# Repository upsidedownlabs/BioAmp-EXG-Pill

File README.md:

BioAmp EXG Pill is a small (2.54 X 1.00 cm) and elegant Analog Front End (AFE) board for BioPotential signal acquisition that you can use with any 5v Micro Controller Unit (MCU) with an ADC. It is capable of recording publication grade BioPotential signals like ECG, EMG, EOG, and EEG without the inclusion of any dedicated Hardware/Software filter, see [BioAmp EXG Pill v0.7 intro video](https://www.youtube.com/watch?v=-G3z9fvQnuw) for more info. The v1.0 of BioAmp EXG pill provides even more flexibilty with configuration option for Gain, BandPass, Filter, and Electrodes.

| Connection      |  Configuration |
| :-------------------------: | :-------------------------: |
|   | |

| Basic Arduino Circuit           |  Electromyography (EMG) |
| :-------------------------: | :-------------------------: |
|   | |

| Electrooculography (EOG) Horizontal           |  Electrooculography (EOG) Vertical |
| :-------------------------: | :-------------------------: |
|   | |

| Electrocardiography (ECG) Lead 1           |  Electroencephalography (EEG) |
| :-------------------------: | :-------------------------: |
|   | |

## Software
BioAmp EXG Pill works with any 5V microcontroller with an ADC like Arduino UNO/Nano or you can use dedicated 5v compatible ADC like ADS1115. To help with signal processing and cleaning you can use the included Arduino example sketches listed below.

| No. | Program| Description |
| ---- | ---- | ---- |
|1 | [FixedSampling](software/FixedSampling)| Sample from ADC at a fixed rate for easy processing of signal.|
|2 | [EMGFilter](software/EMGFilter)| A 74.5 - 149.5 Hz band pass filter sketch for clean Electromyography.|
|3 | [ECGFilter](software/ECGFilter)| A 0.5 - 44.5 Hz band-pass filter sketch for clean Electrocardiography.|
|4 | [EOGFilter](software/EOGFilter)| A 0.5 - 19.5 Hz band-pass filter sketch for clean Electrooculography.|
|5 | [EEGFilter](software/EEGFilter)| A 0.5 - 29.5 Hz band-pass filter sketch for clean Electroencephalography.|
|6 | [EMGEnvelop](software/EMGEnvelop)| EMG signal envelop detection for robotics and biomedical applications.|
|7 | [LEDBarGraph](software/LEDBarGraph)| LED bar graph showing EMG amplitude.|
|8 | [ServoControl](software/ServoControl)| Servo motor control with EMG.|
|9 | [HeartBeatDetection](software/HeartBeatDetection)| Standard deviation based heart beat detection algorithm.|
|10 | [EyeBlinkDetection](software/EyeBlinkDetection)|EOG based eye blink detection.|
|11 | [DrowsinessDetection](software/DrowsinessDetection)| Drowsiness detection using eye blink detection.|
|12 | [ClawController](software/ClawController)| Servo claw controller |
|13 | [EOGPhotoCaptureBLE](software/EOGPhotoCaptureBLE)| EOG based photo clicking machine using ESP32 BLE |
|14 | [Faster_HeartRateDetection](software/Faster_HeartRateDetection)| Faster and more optimzed calculation of BPM |
|15 | [OLED_BPM](software/OLED_BPM)| Display BPM values on OLED Screen|

To-Do:

| No. | Program| Description |
| ---- | ---- | ---- |
|1 | HeartRate | Heart rate calculation with ECG.|
|2 | BrainWaves | Brain waves amplitude with FFT.|
|3 | EOGController | EOG based eye movement detection (left/right) to create a game controller.|

## Hardware

BioAmp EXG Pill has been created using KiCad and all the design files can be found under [hardware](hardware/) folder, including production [Gerber](hardware/gerbers) files. Images below shows a quick overview of the hardware design.

| PCB Front           |  PCB Back |
| :-------------------------: | :-------------------------: |
|   |  |

| Dimensions            |  Schematic  |
| :-------------------------: | :-------------------------: |
|   |  |

## License

| Licenses Facts              |  OSHWA Certification |
| :-------------------------: | :-------------------------: |
|   |  |

#### Hardware
CERN Open Hardware License Version 2 - Strongly Reciprocal ([CERN-OHL-S-2.0](https://spdx.org/licenses/CERN-OHL-S-2.0.html)).

#### Software
MIT open source [license](http://opensource.org/licenses/MIT).

#### Documentation:
<br />This work is licensed under a <a rel="license" href="http://creativecommons.org/licenses/by/4.0/">Creative Commons Attribution 4.0 International License</a>.

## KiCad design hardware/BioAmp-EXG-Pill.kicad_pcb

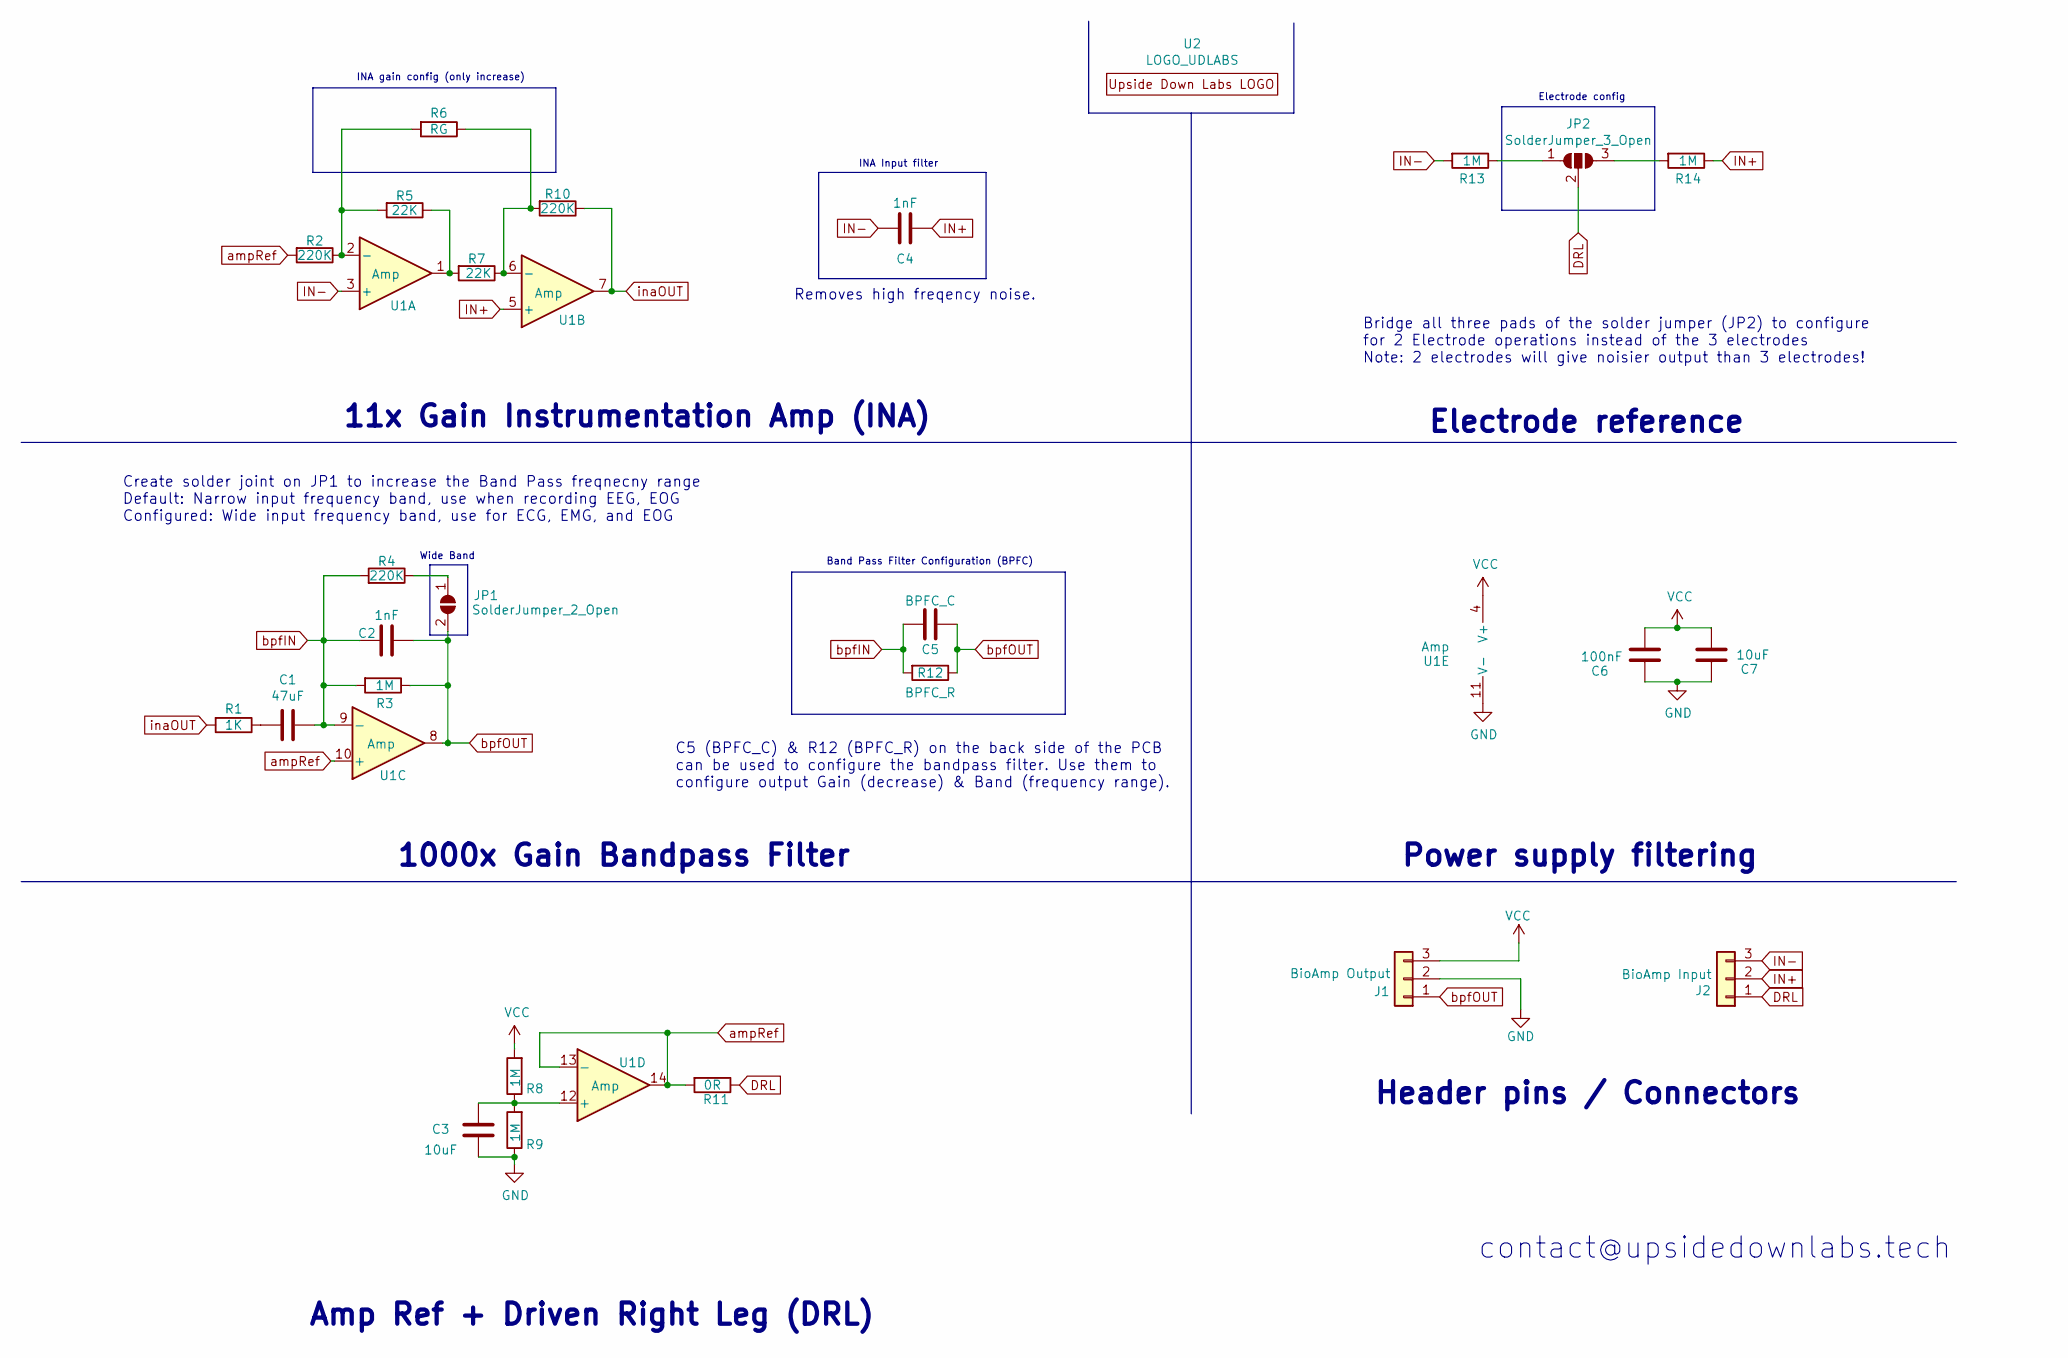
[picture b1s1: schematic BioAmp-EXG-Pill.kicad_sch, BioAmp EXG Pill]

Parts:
C1: 47uF; C_0805_2012Metric_Pad1.18x1.45mm_HandSolder
C2, C4: 1nF; C_0603_1608Metric_Pad1.08x0.95mm_HandSolder
C3, C7: 10uF; C_0603_1608Metric_Pad1.08x0.95mm_HandSolder
C5: BPFC_C; C_0603_1608Metric_Pad1.08x0.95mm_HandSolder
C6: 100nF; C_0603_1608Metric_Pad1.08x0.95mm_HandSolder
J1: BioAmp Output; PinHeader_1x03_P2.54mm_Vertical
J2: BioAmp Input; PinHeader_1x03_P2.54mm_Vertical
JP1: SolderJumper_2_Open; SolderJumper-2_P1.3mm_Open_RoundedPad1.0x1.5mm
JP2: SolderJumper_3_Open; SolderJumper-3_P1.3mm_Open_RoundedPad1.0x1.5mm
R1: 1K; R_0603_1608Metric_Pad0.98x0.95mm_HandSolder
R2, R4, R10: 220K; R_0603_1608Metric_Pad0.98x0.95mm_HandSolder
R3, R8, R9, R13, R14: 1M; R_0603_1608Metric_Pad0.98x0.95mm_HandSolder
R5, R7: 22K; R_0603_1608Metric_Pad0.98x0.95mm_HandSolder
R6: RG; R_0603_1608Metric_Pad0.98x0.95mm_HandSolder
R11: 0R; R_0603_1608Metric_Pad0.98x0.95mm_HandSolder
R12: BPFC_R; R_0603_1608Metric_Pad0.98x0.95mm_HandSolder
U1: Amp; TSSOP-14_4.4x5mm_P0.65mm
U2: LOGO_UDLABS; EXG

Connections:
DRL: J2.1, JP2.2 (C), R11.1; also elsewhere on the board
GND: C3.2, C6.1, C7.1, J1.2, R9.1, U1.11 (V-); also elsewhere on the board
IN+: C4.1, J2.2, R14.1, U1.5 (+); also elsewhere on the board
IN-: C4.2, J2.3, R13.2, U1.3 (+); also elsewhere on the board
unnamed: C1.2, R1.1
unnamed: C3.1, R8.1, R9.2, U1.12 (+)
unnamed: JP1.1 (A), R4.1
unnamed: JP2.1 (A), R13.1
unnamed: JP2.3 (B), R14.2
unnamed: R2.1, R5.2, R6.2, U1.2 (-)
unnamed: R5.1, R7.2, U1.1
unnamed: R6.1, R7.1, R10.2, U1.6 (-)
VCC: C6.2, C7.2, J1.3, R8.2, U1.4 (V+); also elsewhere on the board
ampRef: R2.2, R11.2, U1.10 (+), U1.13 (-), U1.14
bpfIN: C1.1, C2.2, C5.2, R3.2, R4.2, R12.2, U1.9 (-)
bpfOUT: C2.1, C5.1, J1.1, JP1.2 (B), R3.1, R12.1, U1.8; also elsewhere on the board
inaOUT: R1.2, R10.1, U1.7

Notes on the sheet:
contact@upsidedownlabs.tech
1000x Gain Bandpass Filter
Create solder joint on JP1 to increase the Band Pass freqnecny range Default: Narrow input frequency band, use when recording EEG, EOG Configured: Wide input frequency band, use for ECG, EMG, and EOG
Band Pass Filter Configuration (BPFC)
Electrode config
C5 (BPFC_C) & R12 (BPFC_R) on the back side of the PCB can be used to configure the bandpass filter. Use them to configure output Gain (decrease) & Band (frequency range).
Header pins / Connectors
11x Gain Instrumentation Amp (INA)
Bridge all three pads of the solder jumper (JP2) to configure for 2 Electrode operations instead of the 3 electrodes Note: 2 electrodes will give noisier output than 3 electrodes!
Power supply filtering
Amp Ref + Driven Right Leg (DRL)
Removes high freqency noise.
Wide Band
INA gain config (only increase)
Electrode reference
INA Input filter

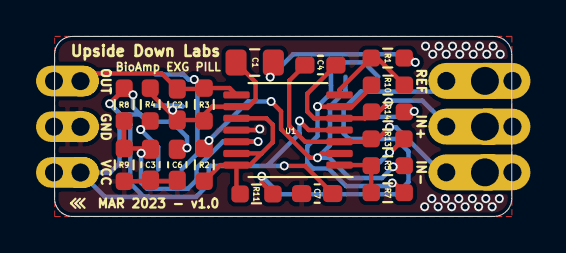
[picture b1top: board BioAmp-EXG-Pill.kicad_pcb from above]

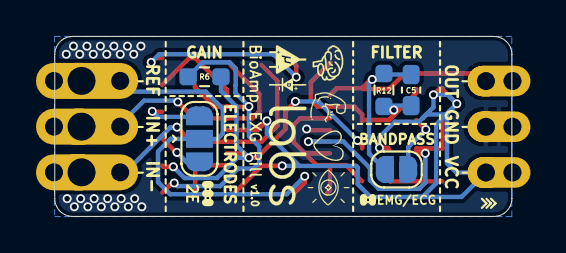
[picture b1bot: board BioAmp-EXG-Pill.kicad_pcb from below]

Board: 2 copper layers, 25.4 x 10.0 mm, 30 parts (6 on the bottom side), 17 nets.

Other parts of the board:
J1#2: BioAmp Output; PinHeader_1x03_P2.54mm_Vertical
J2#2, J2#3: BioAmp Input; PinHeader_1x03_P2.54mm_Vertical

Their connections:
DRL: J2#2.1, J2#3.1; also elsewhere on the board
GND: J1#2.2; also elsewhere on the board
IN+: J2#2.2, J2#3.2; also elsewhere on the board
IN-: J2#2.3, J2#3.3; also elsewhere on the board
VCC: J1#2.3; also elsewhere on the board
bpfOUT: J1#2.1; also elsewhere on the board

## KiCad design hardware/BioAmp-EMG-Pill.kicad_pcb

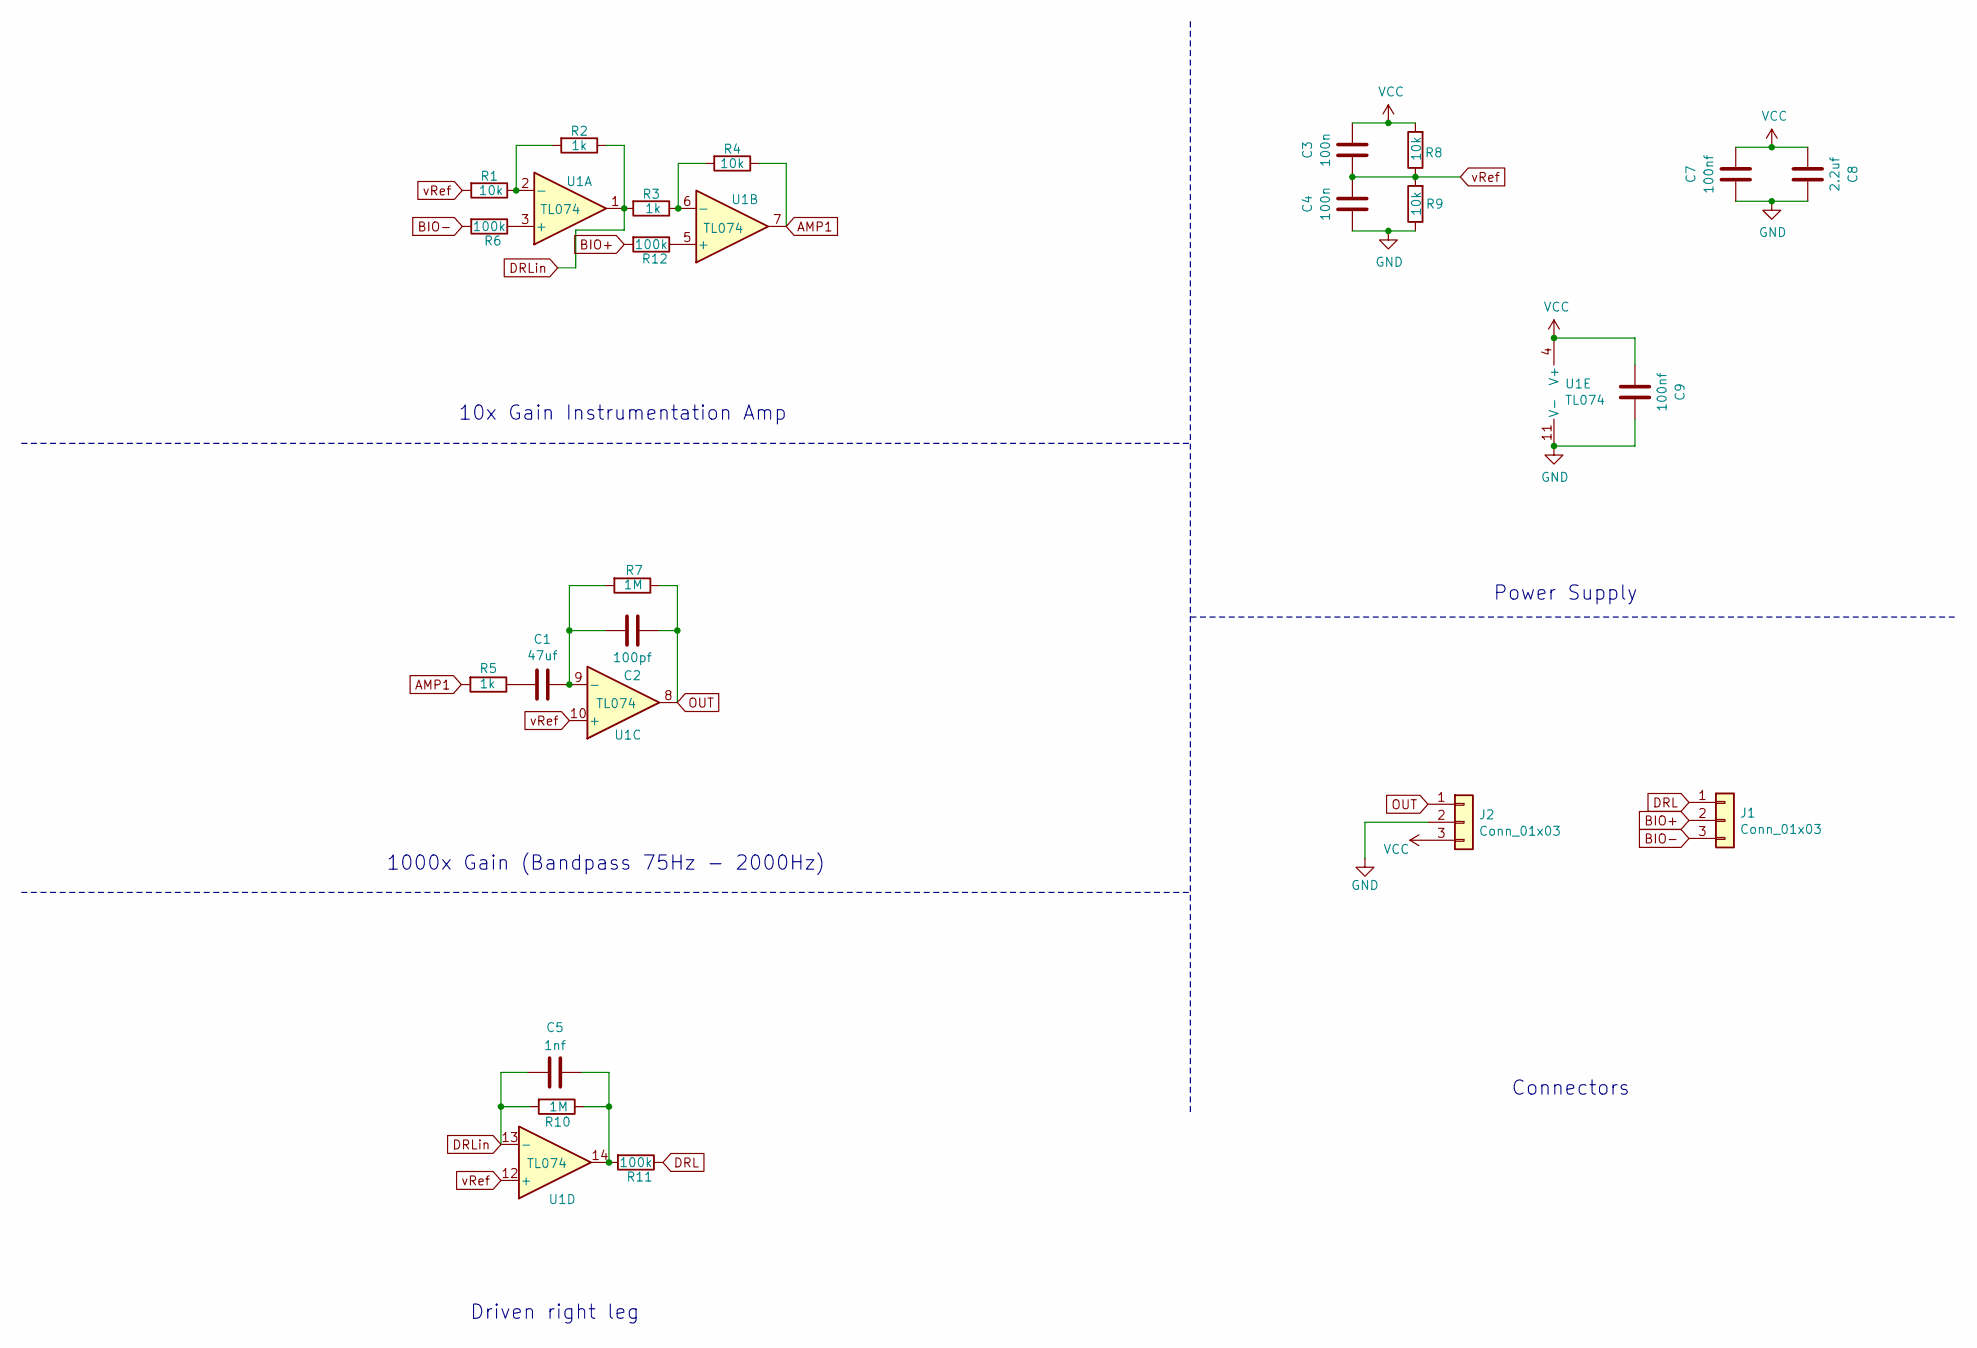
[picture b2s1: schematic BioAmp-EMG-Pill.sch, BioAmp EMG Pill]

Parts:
C1: 47uf; C_0805_2012Metric_Pad1.18x1.45mm_HandSolder
C2: 100pf; C_0603_1608Metric_Pad1.08x0.95mm_HandSolder
C3, C4: 100n; C_0603_1608Metric_Pad1.08x0.95mm_HandSolder
C5: 1nf; C_0603_1608Metric_Pad1.08x0.95mm_HandSolder
C7, C9: 100nf; C_0603_1608Metric_Pad1.08x0.95mm_HandSolder
C8: 2.2uf; C_0603_1608Metric_Pad1.08x0.95mm_HandSolder
J1, J2: Conn_01x03; PinHeader_1x03_P2.54mm_Vertical
R1, R4, R8, R9: 10k; R_0603_1608Metric_Pad0.98x0.95mm_HandSolder
R2, R3, R5: 1k; R_0603_1608Metric_Pad0.98x0.95mm_HandSolder
R6, R11, R12: 100k; R_0603_1608Metric_Pad0.98x0.95mm_HandSolder
R7, R10: 1M; R_0603_1608Metric_Pad0.98x0.95mm_HandSolder
U1: TL074; TSSOP-14_4.4x5mm_P0.65mm

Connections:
AMP1: R4.1, R5.2, U1.7
BIO+: J1.2, R12.2
BIO-: J1.3, R6.2
DRL: J1.1, R11.1
DRLin: C5.1, R2.1, R3.2, R10.2, U1.1, U1.13 (-)
GND: C4.2, C7.2, C8.1, C9.1, J2.2, R9.1, U1.11 (V-)
unnamed: C1.1, C2.2, R7.2, U1.9 (-)
unnamed: C1.2, R5.1
unnamed: C5.2, R10.1, R11.2, U1.14
unnamed: R1.1, R2.2, U1.2 (-)
unnamed: R3.1, R4.2, U1.6 (-)
unnamed: R6.1, U1.3 (+)
unnamed: R12.1, U1.5 (+)
OUT: C2.1, J2.1, R7.1, U1.8
VCC: C3.1, C7.1, C8.2, C9.2, J2.3, R8.2, U1.4 (V+)
vRef: C3.2, C4.1, R1.2, R8.1, R9.2, U1.10 (+), U1.12 (+)

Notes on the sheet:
10x Gain Instrumentation Amp
1000x Gain (Bandpass 75Hz - 2000Hz)
Driven right leg
Power Supply
Connectors

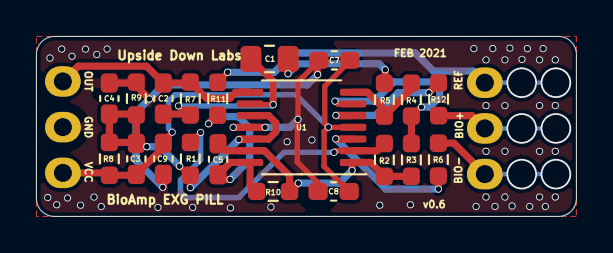
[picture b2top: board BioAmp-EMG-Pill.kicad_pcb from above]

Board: 2 copper layers, 30.0 x 10.0 mm, 23 parts (0 on the bottom side), 16 nets.

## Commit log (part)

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2021-01-27 add shematic
    Schematic for v0.1
2021-01-27 add back image of board
2021-01-27 add board dimensions image
2021-01-30 Update license
2021-01-30 rename image
2021-02-12 add 3D
2021-02-12 Upside Down Labs muscle image
2021-02-18 EMG Pill v0.6 back
2021-02-18 EMG Pill v0.6 Front
2021-02-18 EMG Pill v0.6 dimensions
2021-03-12 Silk layer images
2021-04-10 KiCAD files BioAmp EXG Pill v0.7
    KiCAD (5.1.9) files for Upside Down Labs BioAmp EXG Pill v0.7
2021-04-10 BioAmp EXG panel gerbers
    These are the gerber files for BioAmp EXG Panel, which provides 21 BioAmp EXG Pill on a single PCB.
2021-04-10 BioAmp EXG pill gerbers
    These are the gerber files for BioAmp EXG Pill v0.7
2021-04-10 KiCAD: BioAmp EXG Panel
    KiCAD files for BioAmp EXG Panel which provides 21 BioAmp EXG Pills on a signale PCB.
2021-04-10 Dimensions: BioAmp EXG Pill v0.7
    This image shows the dimensions and the properties (layers) of the BioAmp EXG Pill v0.7 (Taken from KiCAD).
2021-04-10 Schematic: BioAmp EXG Pill v0.7
    This image shows the schematic diagram of the BioAmp EXG Pill v0.7 (Taken from KiCAD).
2021-04-10 BioAmp EXG Pill v0.7
    These image shows the BioAmp EXG Pill v0.7 (Taken from KiCAD and edited with GIMP).
2021-04-10 Magic: BioAmp EXG Pill v0.7
    This image shows design flexibility and the elegance that Upside Down Labs BioAmp EXG Pill v0.7 comes with.
2021-04-10 Update licence
    minimal changes for better alignment and for less markup warnings.
2021-04-10 Update readme
    Updated links and text for BioAmp EXG Pill 0.7
2021-04-11 Update README.md
    Description updated
2021-04-15 Update README.md
    Add shield for Hackaday documentation page!
2021-04-18 OSHW mark image
2021-04-18 Update Readme
    Include OSH Park shared PCB link
2021-04-30 EEG Filter
    Arduino code for recording EEG using BioAmp EXG Pill.
2021-05-01 Update EEGFilter
    Minor code changes implemented.
2021-05-01 ECGFilter frequency response
    Frequency response plot for ECGFilter.
2021-05-02 Recorded ECG image
    Sample ECG recorded with EXG Pill with ECGFilter program.
2021-05-02 EMGFilter frequency response
    Frequency response plot for EMGFilter.
2021-05-02 EOGFilter frequency response
    Frequency response plot for EOGFilter.
2021-05-13 EMG Envelop detection demo video
    This video shows the running EMG and it's envelop detected with the help of EMGEnvelop.ino Arduino code.
2021-05-13 EMG Envelop image
    This static image shows the EMG Envelop detected with EMGEnvelop.ino Arduino code.
2021-05-13 LED bar graph code
    This code is to create a LED bar graph of EMG potential using BioAmp EXG Pill.
2021-05-23 Crowd Supply banner GIF
2021-05-23 Update Readme
    Fix EEG filter frequency text.
2021-05-23 Fix Crowd-Supply link
2021-05-24 HeartBeatDetection.ino serial plotter image
    This image shows the original ECG signal and detected beats on arduino serial plotter with HeartBeatDetection.ino code.
2021-05-27 Eye Blink Detection (Experimental!)
    This is the demo code for eye blink detection based on the heart rate detection. This code is not very accurate at detecting eye blinks and requires improvements.
2021-06-20 BioAmp EXG Pill v0.9 KiCAD PCB
2021-06-20 BioaAmp EXG Pill v0.9 KiCAD schematic
2021-06-24 Update v0.9 schematic part values
2021-06-26 BioAmp EXG Pill v1.0 alpha
    This version of the BioAmp EXG Pill is near to the final release version (v1.0) for the Crowd Supply campaign.
2021-06-26 BioAmp EXG Pill v1.0 alpha PCB
    This version of the BioAmp EXG Pill is near to the final release version (v1.0) for the Crowd Supply campaign.
2021-06-26 BioAmp EXG Pill v1.0a schematic PDF
2021-08-06 Repo cleanup
    Re-arranging all the files and folders for better accessibility.
2021-08-06 Interactive BOM v1.0b
2021-08-06 Texas Instruments LOGO
    Property of Texas Instruments, all right reserved by TI. Adding here just because design uses it.
2021-08-06 Alligator clip SVG
2021-08-06 OSHW certification mark
2021-08-06 Github thumbnail
    Social media preview of the BioAmp EXG Pill
2021-08-06 Fully assembled v0.7
2021-08-06 Crowd Supply Banner
2021-08-06 Magic of BioAmp EXG Pill v1.0b
2021-08-06 BioAmp EXG Pill v1.0b schematic
2021-08-06 v1.0b front annotated
2021-08-06 v1.0b back
2021-08-06 v1.0a front annotated
2021-08-06 v0.7 PCB
2021-08-06 Experimental: Fritzing files
2021-08-06 v1.0b schematic PDF
2021-08-06 v1.0b front PCB
2021-08-12 Claw controller sketch
    This is a demo sketch for controlling claw, it is based on servo controller sketch.
2021-08-12 3D printable claw
    Including 3D printing files of claw and an image
2021-08-12 Servo claw controller sketch (#5)
    * Claw controller sketch
    This is a demo sketch for controlling claw, it is based on servo controller sketch.
    * Update readme
    Updated software examples list with new Claw Controller sketch
    * 3D printable claw
    Including 3D printing files of claw and an image
2021-08-22 Drowsiness Detection sketch
    This updated Drowsiness Detection code now works for Arduino UNO/NANO, ESP32, and other development boards.
2021-08-22 EEG Filter sketch
    This updated EEG Filter code now works for Arduino UNO/NANO, ESP32, and other development boards.
2021-08-22 EMG Filter sketch
    This updated EMG Filter code now works for Arduino UNO/NANO, ESP32, and other development boards.
2021-08-22 EOG Filter sketch
    This updated EOG Filter code now works for Arduino UNO/NANO, ESP32, and other development boards.
2021-08-22 Fixed Sampling sketch
    This updated Fixed Sampling code now works for Arduino UNO/NANO, ESP32, and other development boards.
2021-08-22 LED Bar Graph sketch
    This updated LED Bar Graph Detection code now works for Arduino UNO/NANO, ESP32, and other development boards.
2021-08-22 Servo Control sketch
    This updated Servo Control code now works for Arduino UNO/NANO, ESP32, and other development boards.
2021-08-27 BioAmp EXG PIll with Arduino Nano
    Basic circuit of BioAmp EXG Pill with Arduino nano for recording EMG, ECG, EOG, and EEG.
2021-09-04 EOG based Photo Capture through BLE
    This program uses ESP32 BLE Keyboard functionality to capture photo by detecting eye blinks.
2021-09-04 Basic Circuit
    Basic circuit of BioAmp EXG Pill with Arduino Nano.
2021-09-04 Electrocardiography
2021-09-04 Electroencephalograpy
2021-09-04 Update readme
    Updated readme with circuits.
2021-09-14 EOG Demo
2021-09-14 EOG electrode placements
2021-10-31 Made Footprint and schematic sybols for BioAmp-EXG-Pill module
2021-10-31 Footprint and Symbol libraries for BioAmp-EXG-Pill module
2021-11-01 Kicad Schematic Symbol and Footprint for BioAmp-EXG-Pill (#11)
    * Added footprint for BioAmp-EXG-Pill Module
    * Made Footprint and schematic sybols for BioAmp-EXG-Pill module
    * Added Footprint and Symbol libraries for BioAmp-EXG-Pill module
    * Footprint and Symbol libraries for BioAmp-EXG-Pill module
    * Added Footprint, Symbol and 3D files for Bio-Amp-EXG-pill Module
2021-11-06 Added documentation folder
2021-11-23 added documentation files
2021-11-28 Visualizer 1.0
2021-12-09 added assets file
2021-12-09 solved search issue in docs
2021-12-09 EXG-Visiualizer version 1.0. (#14)
    * Visualizer 1.0
    * Visualizer 1.0
    * Visualizer 1.0
    * Visualizer 1.0
    * changes in frontend
    * changes in frontend
2021-12-17 HeartRateDetector 1.0 added (#16)
    . Heart rate detection was implemented using the R-R interval method.
    . Initialized with 30 R-R intervals for accurate readings.
2022-01-27 Changed theme
2022-01-27 updated theme
2022-01-28 Documentation theme changed (#18)
    * Added footprint for BioAmp-EXG-Pill Module
    * Made Footprint and schematic sybols for BioAmp-EXG-Pill module
    * Added Footprint and Symbol libraries for BioAmp-EXG-Pill module
    * Footprint and Symbol libraries for BioAmp-EXG-Pill module
    * Added Footprint, Symbol and 3D files for Bio-Amp-EXG-pill Module
    * Added documentation folder
2022-05-24 ECG images
    Containing Electrode placement for ECG, sample ECG data recorded using BioAmp EXG pill
2022-05-24 EEG images
    Containing Electrode placement for EEG, sample EEG data recorded using BioAmp EXG pill.
2022-05-24 EEG Updated
    Containing compressed jpg images.
2022-05-24 EMG Updated
    Containing compressed jpg images.
2022-05-24 EOG images
    Containing Electrode placement for EOG, sample EOG data recorded using BioAmp EXG pill.
2022-05-24 Updated Software file
    Containing ECG, EEG, EMG and EOG software files.
2022-05-24 Updated version
    Version changed to v1.0
2022-05-25 Updated images
    images of Bioamp-EXG-pill v1.0
2022-05-25 Updated Software File
    Containing some deleted files and images.
2022-06-05 Added docsify content - pages and images for EOG, ECG, EEG, EMG (#21)
    * Rename filter makdown files
    The names for BioAmp EXG Pill filter code description markdown files has been changed to make it look more understandable for general public. The content will include information about the processing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
    * ECG images
    Containing Electrode placement for ECG, sample ECG data recorded using BioAmp EXG pill
    * ECG file updated
    Containing compressed jpg images.
2022-06-06 Remove space fix #23
    Remove space from images links
2022-07-13 Update images and links (#24)
    Fixes #23
2022-07-17 Sphinx Documentation (#25)
    * Update images and links
    Fixes #23
    * Created Sphinx docs
    created sphinx documentation containing restructured, nojekyll, .gitignore, VERSION files and images.
2022-07-18 added css
    Added css for responsive images and videos
2022-07-18 added break tag
2023-03-09 **Hi lorforlinux, i have added a description about EEG filter**
    i have added a description on what type filter is being used in BioAmp-EXG-Pill and the advantage of using a biquad filter. A more brief description on the filter is required and the picture of the r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
2023-03-10 hello @lorforlinux, I have added the image of filter response.
2023-03-11 Updated the title and format
    hello @lorforlinux, I have made the following changes
    1) added the title
    2) added a line on why is filtering of eeg important
    3) changed the format
2023-03-12 Updated the description of esp32, includes the benefit and the technical specification
    hello @lorforlinux, i have added the description for this page which has the technical specification like the memory, wireless connectivity etc. Also, i've listed the benefits below.
2023-03-16 difference between electrooculogram and electrooculograph is added
    hi @lorforlinux, I've made the changes in terms of the difference between the both mentioned above. gram is the device and graph is the signal that we receive.
2023-03-16 Format of the page has been changed.
    Hello @lorforlinux, I've changed the format for this page.
2023-04-27 Update 3D packages
2023-04-27 Add v1.0 board graphics
2023-04-27 Add interactive BOM v1.0
2023-05-16 Update README.md
    Update v1.0 graphics
2023-05-16 Add v1.0 svg
    Add assembled Pill's svg, renamed front & back specfiacations images
2023-05-16 Update README.md
    update Pill's front and back specifications image
2024-01-03 Constraining servo rotation to 90-180 range. #38 Using defines for servo range and arduino constrain macro to guarantee value is between 90 and 180. Adding clarity to the pause of 10 seconds expresse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
2024-01-12 Improving resolution of servo control. Changing getEnvelop to return a float and using a locally defined mapf to avoid the coarse conversion which happens with int values of 2 to 10. #38
2024-07-09 Update HeartRateDetection.ino
    Updated the data type of avg to uint32_t so as to avoid overflowing of data and changed BPM to uint8_t to maintain it as an integer value.
2024-07-10 New version of HeartRateDetection
    An updated version of BPM calculation with debounced peak detection and more optimized and faster algorithm for peak to peak time calculation.
2024-07-12 OLED_BPM
    Display the Heart Rate(BPM) value on OLED screen connected to development board through I2C.
2024-07-17 Update HeartRateDetection.ino
    Added comment to select the analog input pin accordingly
2024-07-17 Changed the name from HeartRateDetection_V2.0 to Faster_HeartRateDetection
2024-07-19 Update Faster_HeartRateDetection.ino
    Edit some minor corrections

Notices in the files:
README.md:
Open Source Licenses Facts  | Open Source Hardware Certification mark
